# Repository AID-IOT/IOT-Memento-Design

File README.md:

# Memento

A keepsake PCB built at the **AICTE IDEA Lab, Poornima College of Engineering**.
It is a working board as well as a memento: a Seeed XIAO ESP32C3 drives four
WS2812B LEDs and reads a BMP280 pressure/temperature sensor, and serves the
readings on a web page over WiFi. The front silkscreen carries the AICTE IDEA
Lab and Poornima College logos.

| | |
|---|---|
| Board | 150 × 100 mm, 1.6 mm, 2-layer |
| Controller | Seeed Studio XIAO ESP32C3 (RISC-V, WiFi 4 + BLE 5) |
| LEDs | 4 × WS2812B (5050 PLCC-4), daisy-chained |
| Sensor | GY-BMP280-3.3 module, I²C |
| Mounting | 4 × ⌀4.25 mm holes, 13 mm in from each edge |

## Repository layout

```
memento/
├── hw/          KiCad 10 project — schematic, PCB, project library, logo art
│   ├── memento.kicad_sch / .kicad_pcb / .kicad_pro
│   ├── memento.kicad_sym         project symbols
│   ├── memento.pretty/           project footprints
│   ├── assets/                   logo source images
│   └── tools/                    helper scripts (IPC, logo → footprint)
├── sw/          Firmware — builds in PlatformIO *and* opens in Arduino IDE
│   ├── platformio.ini
│   └── memento_fw/
│       ├── memento_fw.ino
│       ├── config.h              ← WiFi name and password go here
│       └── index_html.h          the web page
├── docs/        Project manual (.docx)
│   └── images/                   board renders used in this README
└── README.md
```

## Quick start

**1. Flash the board.** Plug the XIAO into USB-C, then either:

- *Arduino IDE* — open `sw/memento_fw/memento_fw.ino`, select board
  **XIAO_ESP32C3**, install the four Adafruit libraries, upload.
- *PlatformIO* — from `sw/`, run `pio run -t upload`.

Full steps, including the board-manager URL and library list, are in
[`sw/README.md`](sw/README.md).

**2. Set your WiFi.** Before uploading, edit `sw/memento_fw/config.h`:

```c
#define WIFI_SSID       "YOUR_WIFI_NAME"
#define WIFI_PASSWORD   "YOUR_WIFI_PASSWORD"
```

If that network cannot be joined the board starts its own hotspot
(`memento-setup` / `memento123`) so the page is still reachable.

**3. Open the page.** Open the serial monitor at **115200 baud**. It prints the
address it got:

```
Connected. Open http://192.168.1.42/  (or http://memento.local/)
BMP280 found at 0x76
HTTP server up on port 80
```

Browse to that address from any device on the same network. The page shows
temperature, pressure and altitude, refreshing every 2 seconds, and lets you set
the LED mode, colour, brightness and speed.

## Pin map

Taken from `hw/memento.kicad_sch`:

| Signal | XIAO pin | GPIO | Connects to |
|---|---|---|---|
| WS2812B data | D0 | 2 | R1 → D2.DIN → D3 → D4 → D5 |
| I²C SDA | D4 | 6 | U2.SDA, pulled up by R3 |
| I²C SCL | D5 | 7 | U2.SCL, pulled up by R2 |
| +5 V | 5V | — | WS2812B VDD ×4 |
| +3.3 V | 3V3 | — | BMP280 VCC, R2/R3 pull-ups |
| GND | GND | — | all |

## Bill of materials

| Ref | Qty | Part | Package | Notes |
|---|---|---|---|---|
| U1 | 1 | Seeed XIAO ESP32C3 | 14-pin module, 2.54 mm | Hybrid land pattern: headers or castellations |
| U2 | 1 | GY-BMP280-3.3 module | 6-pin, 2.54 mm | Runs from 3V3 |
| D2–D5 | 4 | WS2812B | 5050 PLCC-4 | Addressable RGB |
| R1 | 1 | 330 Ω | 0805 | Series on LED data line |
| R2, R3 | 2 | 4.7 kΩ | 0805 | I²C pull-ups to 3V3 |

> The resistor value fields in the schematic are still at their default
> (`R_US`). The values above are the intended ones — set them in the schematic
> before generating fabrication files.

## Building the PCB

Open `hw/memento.kicad_pro` in **KiCad 10**. The project carries its own symbol
and footprint libraries (`memento.kicad_sym`, `memento.pretty/`) registered
through the project-local `sym-lib-table` and `fp-lib-table`, so it opens
standalone with no external library setup.

The full build process — creating symbols, assigning footprints, importing the
logos to silkscreen, placement, routing and checks — is written up step by step
in the manual under [`docs/`](docs/).

The back side carries only the XIAO and BMP280 through-hole pads and the two
signal vias:

Both renders come straight from the board file, so they can be regenerated after
any layout change:

```bash
kicad-cli pcb render -o docs/images/memento-top.png \
  --side top --preset follow_pcb_editor --quality high \
  --background transparent -w 1800 -h 1240 hw/memento.kicad_pcb
```

Swap `--side top` for `--side bottom` for the other view. The
`follow_pcb_editor` preset matters: the default `follow_plot_settings` drops the
silkscreen, which renders the board as a blank rectangle with no logos.

## Documentation

| File | What it covers |
|---|---|
| [`docs/`](docs/) | Project manual (.docx) — full KiCad workflow, BOM, programming, usage |
| [`sw/README.md`](sw/README.md) | Firmware setup, libraries, HTTP API, hardware notes |

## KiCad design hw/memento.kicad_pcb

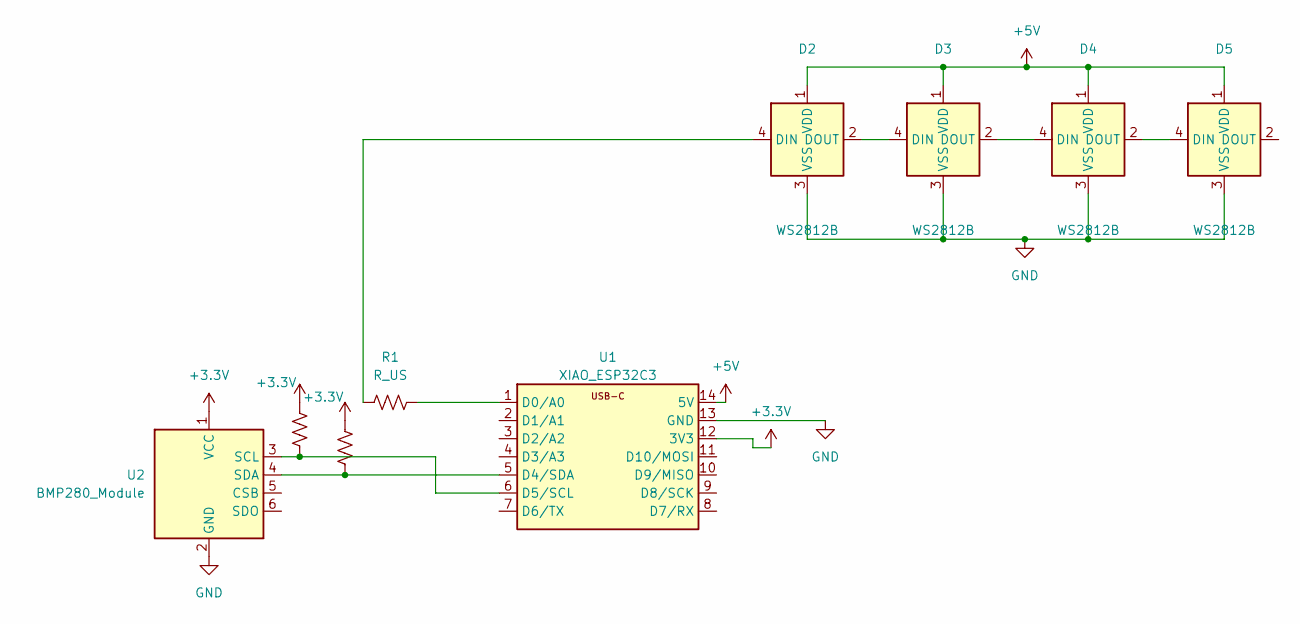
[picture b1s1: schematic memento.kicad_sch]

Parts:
D2, D3, D4, D5: WS2812B; WS2812B_PLCC4_5.0x5.0mm
R1, R2, R3: R_US; R_0805_2012Metric
U1: XIAO_ESP32C3; XIAO-ESP32C3-Hybrid
U2: BMP280_Module; BMP280_Module_GY_6P_15x11.5mm

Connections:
+3.3V: R2.2, R3.2, U1.12 (3V3), U2.1 (VCC)
+5V: D2.1 (VDD), D3.1 (VDD), D4.1 (VDD), D5.1 (VDD), U1.14 (5V)
GND: D2.3 (VSS), D3.3 (VSS), D4.3 (VSS), D5.3 (VSS), U1.13 (GND), U2.2 (GND)
unnamed: D2.4 (DIN), R1.1
unnamed: D2.2 (DOUT), D3.4 (DIN)
unnamed: D3.2 (DOUT), D4.4 (DIN)
unnamed: D4.2 (DOUT), D5.4 (DIN)
unnamed: R1.2, U1.1 (D0/A0)
unnamed: R3.1, U1.5 (D4/SDA), U2.4 (SDA)
unnamed: R2.1, U1.6 (D5/SCL), U2.3 (SCL)

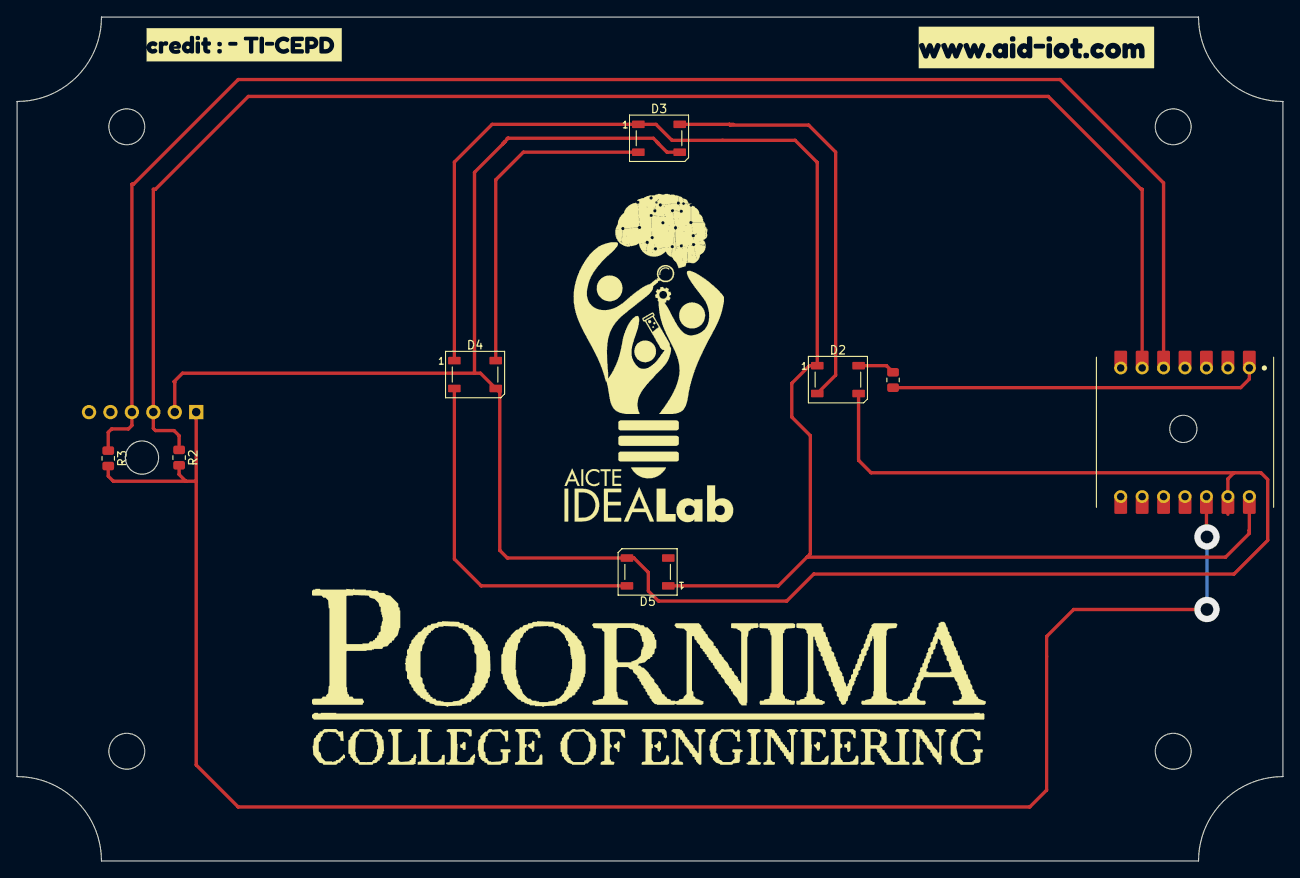
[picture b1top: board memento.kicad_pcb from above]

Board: 2 copper layers, 150.0 x 100.0 mm, 13 parts (1 on the bottom side), 10 nets.

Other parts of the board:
LOGO1: Logo_AICTE_IDEALab
LOGO2: Logo_Poornima_80x48
kibuzzard-6AB62C58: G***; kibuzzard-6AB62C58
kibuzzard-6AB62C70: G***; kibuzzard-6AB62C70
